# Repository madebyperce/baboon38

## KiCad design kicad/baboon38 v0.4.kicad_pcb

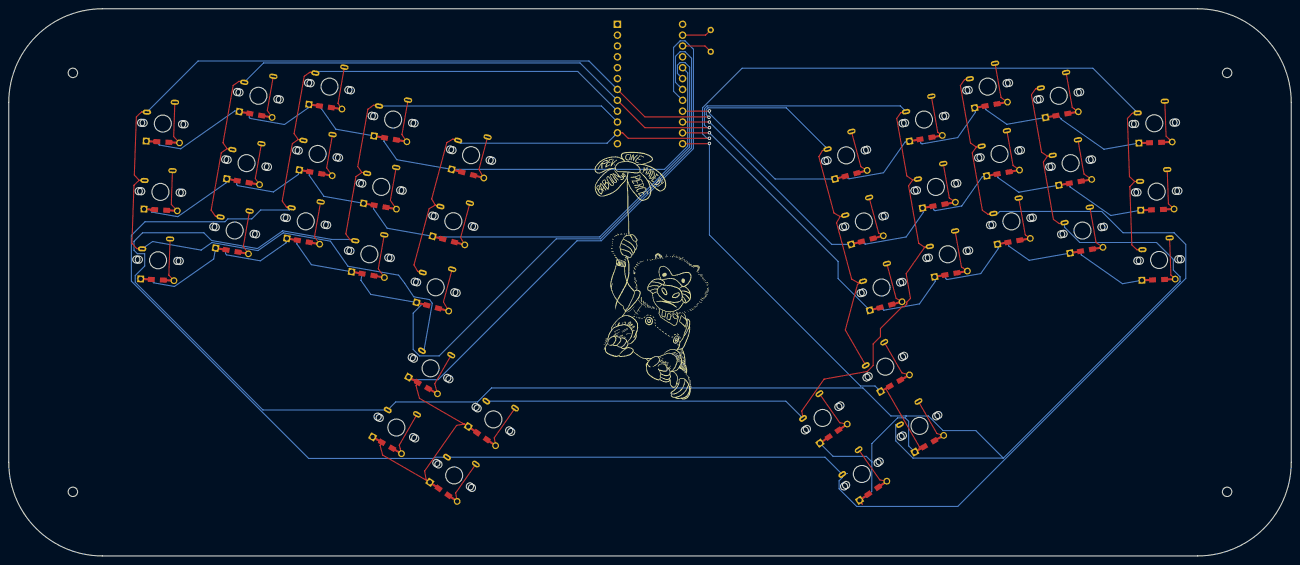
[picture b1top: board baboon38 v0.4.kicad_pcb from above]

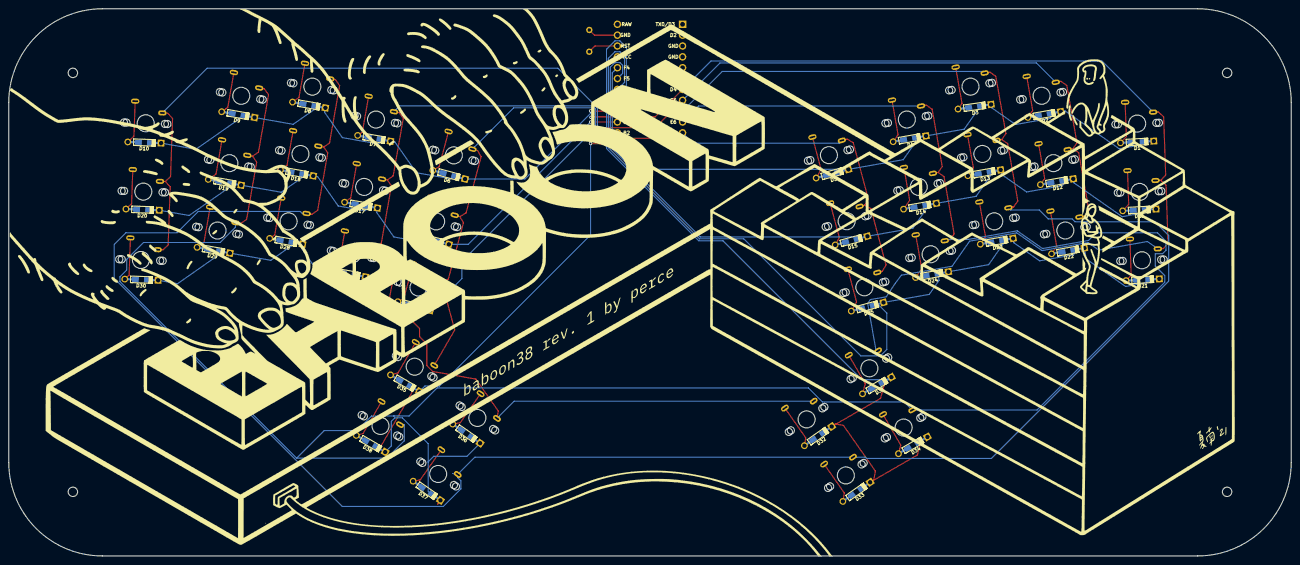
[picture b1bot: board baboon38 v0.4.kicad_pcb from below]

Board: 2 copper layers, 300.0 x 128.0 mm, 78 parts (39 on the bottom side), 53 nets.

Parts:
D1, D2, D3, D4, D5, D6, D7, D8, D9, D10, D11, D12, D13, D14, D15, D16, D17, D18, D19, D20, D21, D22, D23, D24, D25, D26, D27, D28, D29, D30, D31, D32, D33, D34, D35, D36, D37, D38: D_Small; Diode-dual
MX1, MX2, MX3, MX4, MX5, MX6, MX7, MX8, MX9, MX10, MX11, MX12, MX13, MX14, MX15, MX16, MX17, MX18, MX19, MX20, MX21, MX22, MX23, MX24, MX25, MX26, MX27, MX28, MX29, MX30, MX31, MX32, MX33, MX34, MX35, MX36, MX37, MX38: MX-1U; CherryMX_MidHeight_16mm_rev2
SW1: SW_Push; tact_switch_5mm_noborder
U1: ProMicro; ArduinoProMicro-TopSide

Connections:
GND: SW1.2, U1.3, U1.4, U1.23
unnamed: D1.2, MX1.2
unnamed: D2.2, MX2.2
unnamed: D3.2, MX3.2
unnamed: D4.2, MX4.2
unnamed: D5.2, MX5.2
unnamed: D6.2, MX6.2
unnamed: D7.2, MX7.2
unnamed: D8.2, MX8.2
unnamed: D9.2, MX9.2
unnamed: D10.2, MX10.2
unnamed: D11.2, MX11.2
unnamed: D12.2, MX12.2
unnamed: D13.2, MX13.2
unnamed: D14.2, MX14.2
unnamed: D15.2, MX15.2
unnamed: D16.2, MX16.2
unnamed: D17.2, MX17.2
unnamed: D18.2, MX18.2
unnamed: D19.2, MX19.2
unnamed: D20.2, MX20.2
unnamed: D21.2, MX21.2
unnamed: D22.2, MX22.2
unnamed: D23.2, MX23.2
unnamed: D24.2, MX24.2
unnamed: D25.2, MX25.2
unnamed: D26.2, MX26.2
unnamed: D27.2, MX27.2
unnamed: D28.2, MX28.2
unnamed: D29.2, MX29.2
unnamed: D30.2, MX30.2
unnamed: D31.2, MX31.2
unnamed: D32.2, MX32.2
unnamed: D33.2, MX33.2
unnamed: D34.2, MX34.2
unnamed: D35.2, MX35.2
unnamed: D36.2, MX36.2
unnamed: D37.2, MX37.2
unnamed: D38.2, MX38.2
col0: MX1.1, MX6.1, MX11.1, MX16.1, MX21.1, MX26.1, MX31.1, MX35.1, U1.7
col1: MX2.1, MX7.1, MX12.1, MX17.1, MX22.1, MX27.1, MX32.1, MX36.1, U1.8
col2: MX3.1, MX8.1, MX13.1, MX18.1, MX23.1, MX28.1, MX33.1, MX37.1, U1.9
col3: MX4.1, MX9.1, MX14.1, MX19.1, MX24.1, MX29.1, MX34.1, MX38.1, U1.10
col4: MX5.1, MX10.1, MX15.1, MX20.1, MX25.1, MX30.1, U1.11
reset: SW1.1, U1.22
row0: D1.1, D2.1, D3.1, D4.1, D5.1, U1.20
row1: D11.1, D12.1, D13.1, D14.1, D15.1, U1.19
row2: D21.1, D22.1, D23.1, D24.1, D25.1, U1.18
row3: D31.1, D32.1, D33.1, D34.1, U1.17
row4: D6.1, D7.1, D8.1, D9.1, D10.1, U1.16
row5: D16.1, D17.1, D18.1, D19.1, D20.1, U1.15
row6: D26.1, D27.1, D28.1, D29.1, D30.1, U1.14
row7: D35.1, D36.1, D37.1, D38.1, U1.13

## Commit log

2021-08-10 add photos
2021-08-10 enhance
2021-08-10 delete
2021-08-10 try again
2021-08-10 again!!!
